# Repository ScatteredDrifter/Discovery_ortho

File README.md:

# SO[H] ORTHO!

A 52 key (4x14) ortholinear keyboard, powered by an RP2040

This is a fork of [Horizon by skarrmann](https://github.com/skarrmann/horizon)

Used License [MIT](/LICENSE)

 ---
This keyboard is a grid of 1U keys with optional hotswap, breakout for LED-backlighting.

## Status :: 
- prototypes arrived and **working**
- Case to be tested 
- untested LEDs
- untested LED-Pinout
- working encoder  

---

## Features :: 
- QMK and Vial Support
- Support for Choc-Switches **only**!
- Choc-spacing 
- Hotswap for Choc-Switches 
- built with rp2040 and additional flash storage allowing for plenty of combos, layers, led matrices etc.
- easy to order with jlcpcb --> check release for files 
- support for encoder in the middle  
- additional pinouts for further modifications 
- middle part features several layouts

## Layout :: 

This pcb features different layouts that are configured within VIAL for easy usage. See below for available Layout-Options. 

As for the case, there are 6 screw holes for mounting a panel in the middle to cover the electronics. 

## Firmware :: 

the pre-compiled file for Vial and the whole Qmk-userspace for this keyboard can be found [here](/firmware/)

To enter the bootloader - which is necessary in order to flash a new firmware - you'll have to bridge the two contacts located in the middle of the front-pcb. In later revisions there might be actual buttons, for the first revision I was not able to get them to fit on there. Bridge both contacts for a short amount of time in order to boot the mcu to bootloader. It should show up as a regular usb-stick in your file explorer now and you can drag the .utf onto this usb-stick. Once done it will restart and use your newly flashed firmware!

## Images of PCB ::

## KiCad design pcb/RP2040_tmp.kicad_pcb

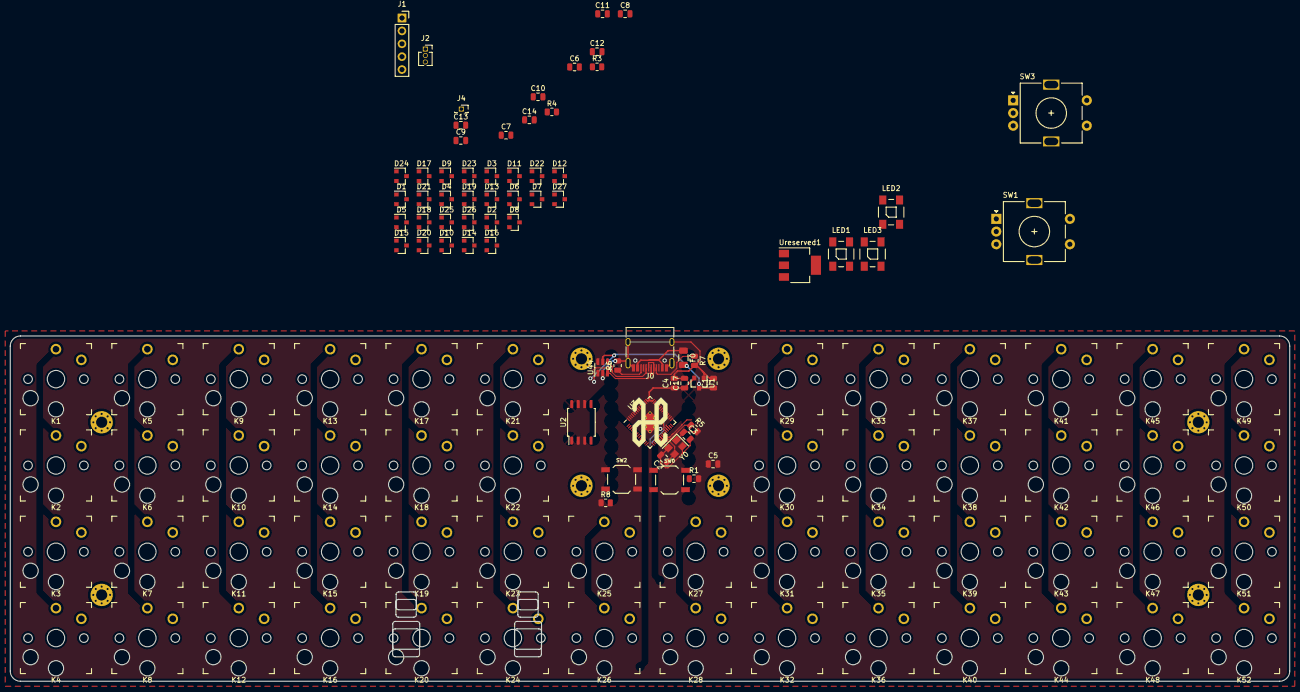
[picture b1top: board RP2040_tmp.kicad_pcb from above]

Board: 2 copper layers, 252.0 x 68.0 mm, 129 parts (1 on the bottom side), 99 nets.

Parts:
C1, C4, C17: 10u; C_0805_2012Metric
C2, C3: 22pf; C_0805_2012Metric
C5, C6, C7, C9, C11, C12, C13, C14: 100n; C_0805_2012Metric
C8, C10: 1u; C_0805_2012Metric
D1, D2, D3, D4, D5, D6, D7, D8, D9, D10, D11, D12, D13, D14, D15, D16, D17, D18, D19, D20, D21, D22, D23, D24, D25, D26, D27: BAV70; SOT-23
F0: polyfuse; Fuse_1206_3216Metric
H1, H2, H3, H4, H5, H6, H7, H8: Hole_Pad; Mount_M2
J0: USB_C_Receptacle_USB2.0; USB_C_Receptacle_HRO_TYPE-C-31-M-12
J1: BREAKOUT; PinSocket_1x05_P2.54mm_Vertical
J2: Conn_01x03_Male; PinSocket_1x03_P1.27mm_Vertical
J4: Conn_01x01_Male; PinSocket_1x01_P1.27mm_Vertical
K1, K2, K3, K4, K5, K6, K7, K8, K9, K10, K11, K12, K13, K14, K15, K16, K17, K18, K19, K20, K21, K22, K23, K24, K25, K26, K27, K28, K29, K30, K31, K32, K33, K34, K35, K36, K37, K38, K39, K40, K41, K42, K43, K44, K45, K46, K47, K48, K49, K50, K51, K52: KEYSW; Kailh_socket_PG1350_optional
LED1, LED2, LED3: WS2812B
LOGO1: Logo-Bottom; Logo_Horizon_Small
LOGO2: Logo-Top; Logo_Horizon_H
R1, R5: 1k; R_0805_2012Metric
R3, R4: 27; R_0805_2012Metric
R6, R7: 5.1k; R_0805_2012Metric
R8: 10k; R_0805_2012Metric
SW0, SW2: RESET; SW_SPST_TL3342
SW1, SW3: RotaryEncoder_Switch; RotaryEncoder_Alps_EC11E-Switch_Vertical_H20mm
U1: XC6206 smaller footprint; SOT-23
U2: W25Q128JVS; SOIC-8_5.23x5.23mm_P1.27mm
U3: RP2040; RP2040-QFN-56
U44: SRV05-4; SOT-23-6
Ureserved1: larger footprint, more mA available; SOT-223-3_TabPin2
Y0: 12MHZ Crystal; Crystal_SMD_3225-4Pin_3.2x2.5mm

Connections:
+1V1: C6.1, C7.1, C8.1, J4.1, U3.23 (DVDD), U3.45 (VREG_VOUT), U3.50 (DVDD)
+3V3: C4.1, C5.1, C9.1, C10.1, C11.1, C12.1, C13.1, C14.1, C17.1, J1.2, R8.2, U1.2 (VO), U2.8 (VCC), U3.1 (IOVDD), U3.10 (IOVDD), U3.22 (IOVDD), U3.33 (IOVDD), U3.42 (IOVDD), U3.43 (ADC_AVDD), U3.44 (VREG_IN), U3.48 (USB_VDD), U3.49 (IOVDD)
+5V: C1.1, F0.2, J2.1, LED1.1 (VCC), LED2.1 (VCC), LED3.1 (VCC), U1.3 (VI), U44.5 (VP)
/QSPI_SCLK: U2.6 (CLK), U3.52 (QSPI_SCLK)
/QSPI_SD0: U2.5 (DI(IO0)), U3.53 (QSPI_SD0)
/QSPI_SD1: U2.2 (DO(IO1)), U3.55 (QSPI_SD1)
/QSPI_SD2: U2.3 (IO2), U3.54 (QSPI_SD2)
/QSPI_SD3: U2.7 (IO3), U3.51 (QSPI_SD3)
/QSPI_SS: R1.1, U2.1 (~CS), U3.56 (QSPI_SS)
/RUN: J1.1, R8.1, SW2.2, U3.26 (RUN)
/SWCLK: J1.5, U3.24 (SWCLK)
/SWD: J1.4, U3.25 (SWD)
/USB_D+: J0.A6 (D+), J0.B6 (D+), R3.1, U44.4 (IO3)
/USB_D-: J0.A7 (D-), J0.B7 (D-), R4.1, U44.3 (IO2)
/XIN: C2.1, U3.20 (XIN), Y0.3
/XOUT: R5.1, U3.21 (XOUT)
/~USB_BOOT: R1.2, SW0.2
COL0: K1.2, K2.2, K3.2, K4.2, U3.37 (GPIO25)
COL1: K5.1, K6.1, K7.1, K8.1, U3.36 (GPIO24)
COL2: K9.2, K10.2, K11.2, K12.2, U3.35 (GPIO23)
COL3: K13.1, K14.1, K15.1, K16.1, U3.34 (GPIO22)
COL4: K17.2, K18.2, K19.2, K20.2, U3.32 (GPIO21)
COL5: K21.1, K22.1, K23.1, K24.1, U3.31 (GPIO20)
COL6: K25.2, K26.2, SW1.S2, U3.30 (GPIO19)
COL7: K27.1, K28.1, SW3.S1, U3.29 (GPIO18)
COL8: K29.2, K30.2, K31.2, K32.2, U3.28 (GPIO17)
COL9: K33.1, K34.1, K35.1, K36.1, U3.27 (GPIO16)
COL10: K37.2, K38.2, K39.2, K40.2, U3.18 (GPIO15)
COL11: K41.1, K42.1, K43.1, K44.1, U3.17 (GPIO14)
COL12: K45.2, K46.2, K47.2, K48.2, U3.15 (GPIO12)
COL13: K49.1, K50.1, K51.1, K52.1, U3.14 (GPIO11)
GND: C1.2, C2.2, C3.2, C4.2, C5.2, C6.2, C7.2, C8.2, C9.2, C10.2, C11.2, C12.2, C13.2, C14.2, C17.2, J0.A1 (GND), J0.A12 (GND), J0.B1 (GND), J0.B12 (GND), J0.S1 (SHIELD), J1.3, J2.2, LED1.3 (GND), LED2.3 (GND), LED3.3 (GND), R6.2, R7.2, SW0.1, SW1.C, SW2.1, SW3.C, U1.1 (GND), U2.4 (GND), U3.19 (TESTEN), U3.57 (GND), U44.2 (VN), Y0.2, Y0.4
LED_GLOW: J2.3, LED1.4 (DIN), U3.8 (GPIO6)
unnamed: C3.1, R5.2, Y0.1
unnamed: D1.1 (A), K1.1
unnamed: D1.2 (A), K5.2
unnamed: D2.1 (A), K2.1
unnamed: D2.2 (A), K6.2
unnamed: D3.1 (A), K3.1
unnamed: D3.2 (A), K7.2
unnamed: D4.1 (A), K4.1
unnamed: D4.2 (A), K8.2
unnamed: D5.1 (A), K9.1
unnamed: D5.2 (A), K13.2
unnamed: D6.1 (A), K10.1
unnamed: D6.2 (A), K14.2
unnamed: D7.1 (A), K11.1
unnamed: D7.2 (A), K15.2
unnamed: D8.1 (A), K12.1
unnamed: D8.2 (A), K16.2
unnamed: D9.1 (A), K17.1
unnamed: D9.2 (A), K21.2
unnamed: D10.1 (A), K18.1
unnamed: D10.2 (A), K22.2
unnamed: D11.1 (A), K19.1
unnamed: D11.2 (A), K23.2
unnamed: D12.1 (A), K20.1
unnamed: D12.2 (A), K24.2
unnamed: D13.1 (A), SW1.S1
unnamed: D13.2 (A), SW3.S2
unnamed: D14.1 (A), K25.1
unnamed: D14.2 (A), K27.2
unnamed: D15.1 (A), K26.1
unnamed: D15.2 (A), K28.2
unnamed: D16.1 (A), K29.1
unnamed: D16.2 (A), K33.2
unnamed: D17.1 (A), K30.1
unnamed: D17.2 (A), K34.2
unnamed: D18.1 (A), K31.1
unnamed: D18.2 (A), K35.2
unnamed: D19.1 (A), K32.1
unnamed: D19.2 (A), K36.2
unnamed: D20.1 (A), K37.1
unnamed: D20.2 (A), K41.2
unnamed: D21.1 (A), K38.1
unnamed: D21.2 (A), K42.2
unnamed: D22.1 (A), K39.1
unnamed: D22.2 (A), K43.2
unnamed: D23.1 (A), K40.1
unnamed: D23.2 (A), K44.2
unnamed: D24.1 (A), K45.1
unnamed: D24.2 (A), K49.2
unnamed: D25.1 (A), K46.1
unnamed: D25.2 (A), K50.2
unnamed: D26.1 (A), K47.1
unnamed: D26.2 (A), K51.2
unnamed: D27.1 (A), K48.1
unnamed: D27.2 (A), K52.2
unnamed: J0.A5 (CC1), R7.1
unnamed: J0.B5 (CC2), R6.1
unnamed: LED1.2 (DOUT), LED2.4 (DIN)
unnamed: LED2.2 (DOUT), LED3.4 (DIN)
unnamed: R3.2, U3.47 (USB_DP)
unnamed: R4.2, U3.46 (USB_DM)
ROW0: D1.3 (K), D5.3 (K), D9.3 (K), D16.3 (K), D20.3 (K), D24.3 (K), U3.7 (GPIO5)
ROW1: D2.3 (K), D6.3 (K), D10.3 (K), D13.3 (K), D17.3 (K), D21.3 (K), D25.3 (K), U3.6 (GPIO4)
ROW2: D3.3 (K), D7.3 (K), D11.3 (K), D14.3 (K), D18.3 (K), D22.3 (K), D26.3 (K), U3.9 (GPIO7)
ROW3: D4.3 (K), D8.3 (K), D12.3 (K), D15.3 (K), D19.3 (K), D23.3 (K), D27.3 (K), U3.12 (GPIO9)
VBUS: F0.1, J0.A4 (VBUS), J0.A9 (VBUS), J0.B4 (VBUS), J0.B9 (VBUS)

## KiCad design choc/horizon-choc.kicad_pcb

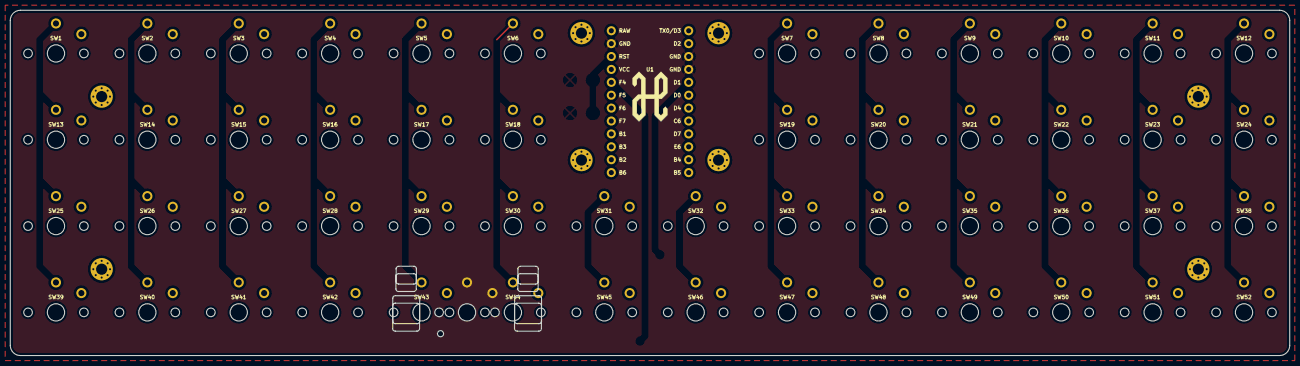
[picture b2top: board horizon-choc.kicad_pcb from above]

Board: 2 copper layers, 252.0 x 68.0 mm, 63 parts (1 on the bottom side), 15 nets.

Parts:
H1, H2, H3, H4, H5, H6, H7, H8: Hole_Pad; Mount_M2
LOGO1: Logo-Bottom; Logo_Horizon_Small
LOGO2: Logo-Top; Logo_Horizon_H
SW1, SW2, SW3, SW4, SW5, SW6, SW7, SW8, SW9, SW10, SW11, SW12, SW13, SW14, SW15, SW16, SW17, SW18, SW19, SW20, SW21, SW22, SW23, SW24, SW25, SW26, SW27, SW28, SW29, SW30, SW31, SW32, SW33, SW34, SW35, SW36, SW37, SW38, SW39, SW40, SW41, SW42, SW43, SW44, SW45, SW46, SW47, SW48, SW49, SW50, SW51, SW52: SW_Push; SW_Choc
U1: PRO-MICRO; Pro-Micro

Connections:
COL1: SW1.1, SW13.1, SW25.1, SW39.1, U1.19
COL2: SW2.1, SW14.1, SW26.1, SW40.1, U1.18
COL3: SW3.1, SW15.1, SW27.1, SW41.1, U1.17
COL4: SW4.1, SW16.1, SW28.1, SW42.1, U1.16
COL5: SW5.1, SW17.1, SW29.1, SW43.1, U1.15
COL6: SW6.1, SW18.1, SW30.1, SW44.1, U1.14
COL7: SW31.1, SW45.1, U1.13
COL8: SW32.1, SW46.1, U1.12
COL9: SW7.1, SW19.1, SW33.1, SW47.1, U1.11
COL10: SW8.1, SW20.1, SW34.1, SW48.1, U1.10
COL11: SW9.1, SW21.1, SW35.1, SW49.1, U1.9
COL12: SW10.1, SW22.1, SW36.1, SW50.1, U1.8
COL13: SW11.1, SW23.1, SW37.1, SW51.1, U1.7
COL14: SW12.1, SW24.1, SW38.1, SW52.1, U1.6
GND: U1.3, U1.4, U1.23

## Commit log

2022-10-17 first commit, reduced quantity
2022-10-19 updated pcb
2022-10-26 updated pcb
    added onboard mcu
    included silkscreen resembling sun and SOHO
    added files for assembly with jlcpcb
2022-11-02 fixed issue of pcb, added assembly files for jlc
2022-12-01 updated Readme, restructured repo
    - added further information and images to readme
    - added directory for firmware
    - kle.json to be found on repo
